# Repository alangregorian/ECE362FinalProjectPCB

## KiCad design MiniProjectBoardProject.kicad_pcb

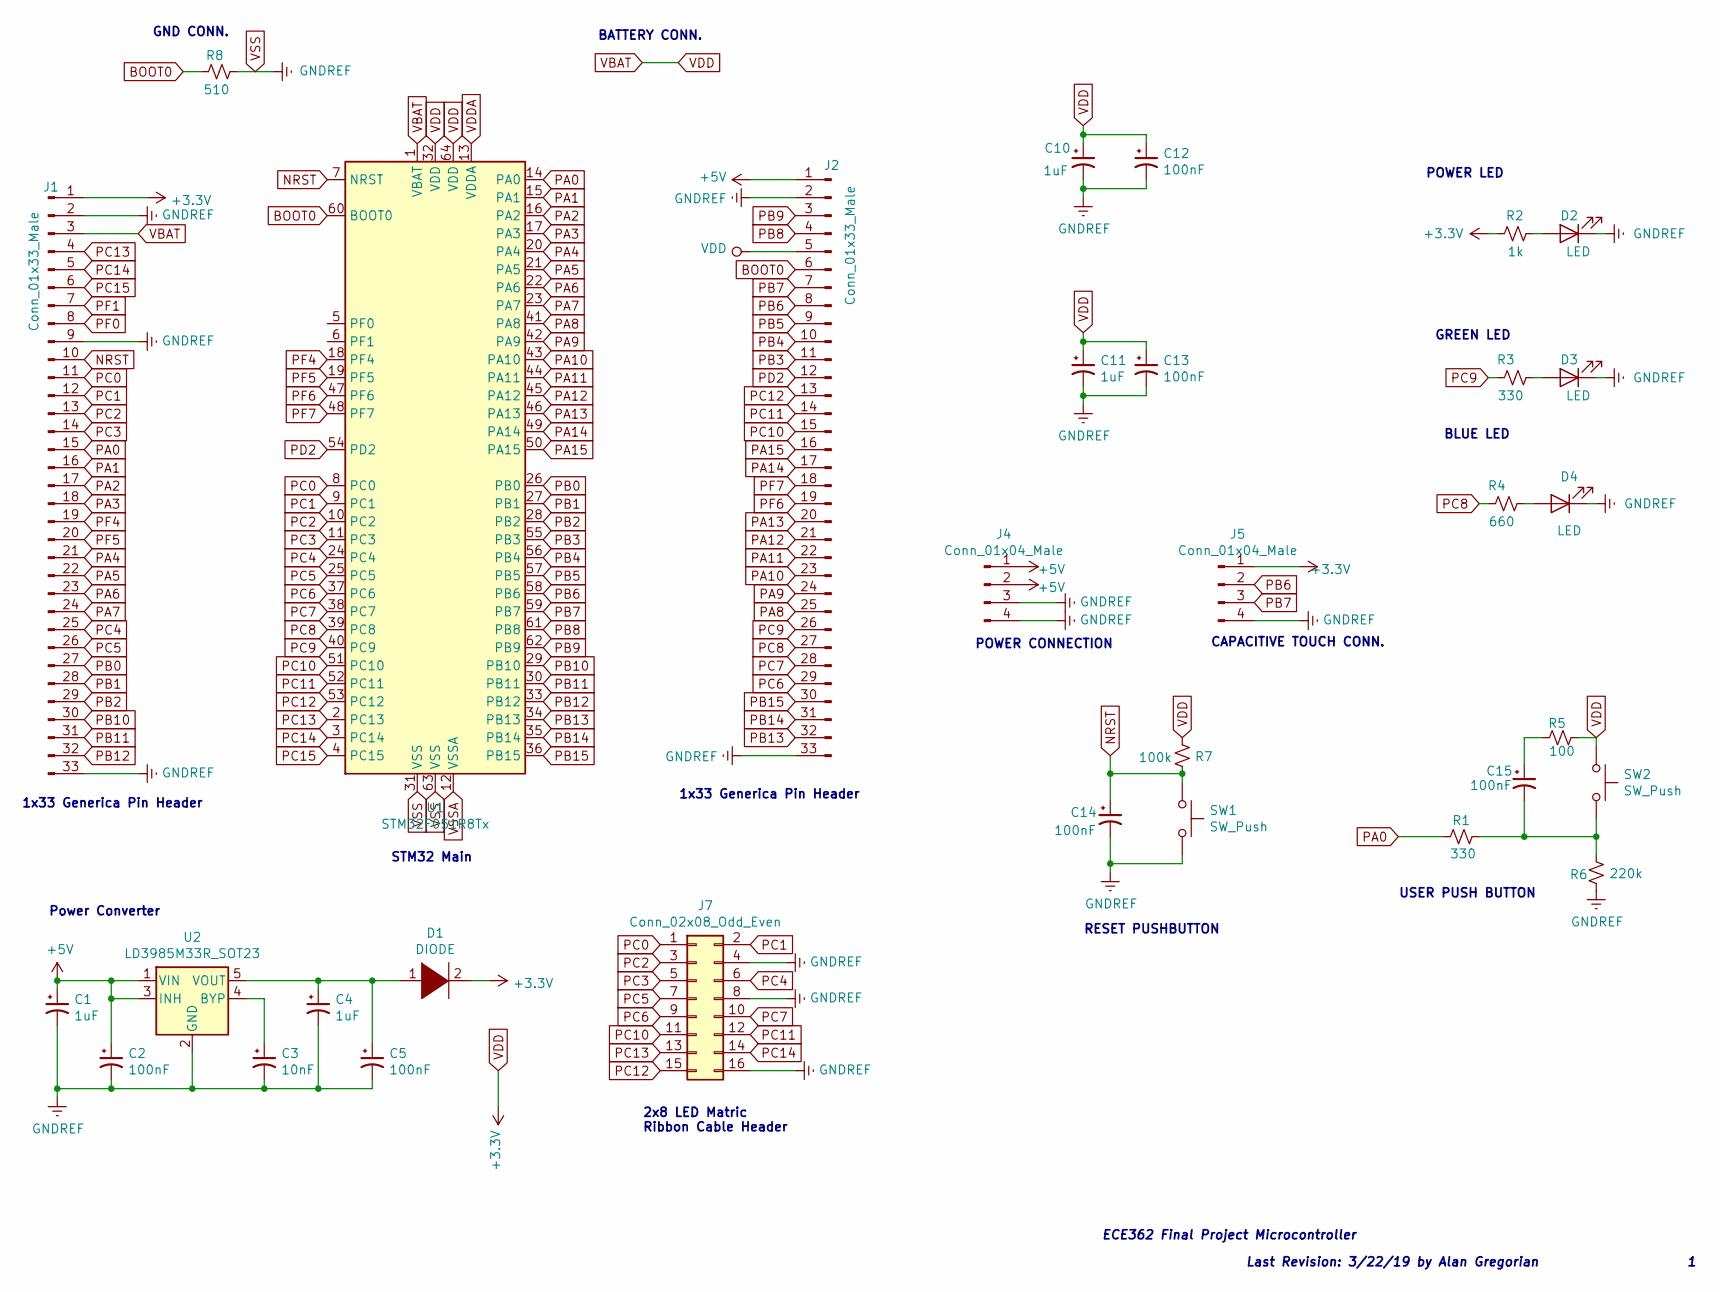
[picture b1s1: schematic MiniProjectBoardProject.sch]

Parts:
C1, C4, C10, C11: 1uF; C_0201_0603Metric
C2, C5, C12, C13, C14, C15: 100nF; C_0201_0603Metric
C3: 10nF; C_0201_0603Metric
D1: DIODE; D_SOD-323
D2, D3, D4: LED; LED_1206_3216Metric
J1, J2: Conn_01x33_Male; PinSocket_1x33_P2.54mm_Vertical
J4, J5: Conn_01x04_Male; PinSocket_1x04_P2.54mm_Vertical
J7: Conn_02x08_Odd_Even; PinSocket_2x08_P2.54mm_Vertical
R1, R3: 330; R_0603_1608Metric
R2: 1k; R_0603_1608Metric
R4: 660; R_0603_1608Metric
R5: 100; R_0603_1608Metric
R6: 220k; R_0603_1608Metric
R7: 100k; R_0603_1608Metric
R8: 510; R_0603_1608Metric
SW1, SW2: SW_Push; SW_PUSH_6mm
U1: STM32F051R8Tx; LQFP-64_10x10mm_P0.5mm
U2: LD3985M33R_SOT23; SOT-23-5

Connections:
+5V: C1.1, C2.1, J2.1, J4.1, J4.2, U2.1 (VIN), U2.3 (INH)
BOOT0: J2.6, R8.1, U1.60 (BOOT0)
NRST: C14.1, J1.10, R7.1, SW1.1, U1.7 (NRST)
unnamed: C3.1, U2.4 (BYP)
unnamed: C4.1, C5.1, D1.1 (K), U2.5 (VOUT)
unnamed: C15.1, R5.2
unnamed: C15.2, R1.1, R6.2, SW2.2
unnamed: D2.2 (A), R2.1
unnamed: D3.2 (A), R3.1
unnamed: D4.2 (A), R4.1
PA0: J1.15, R1.2, U1.14 (PA0)
PA1: J1.16, U1.15 (PA1)
PA2: J1.17, U1.16 (PA2)
PA3: J1.18, U1.17 (PA3)
PA4: J1.21, U1.20 (PA4)
PA5: J1.22, U1.21 (PA5)
PA6: J1.23, U1.22 (PA6)
PA7: J1.24, U1.23 (PA7)
PA8: J2.25, U1.41 (PA8)
PA9: J2.24, U1.42 (PA9)
PA10: J2.23, U1.43 (PA10)
PA11: J2.22, U1.44 (PA11)
PA12: J2.21, U1.45 (PA12)
PA13: J2.20, U1.46 (PA13)
PA14: J2.17, U1.49 (PA14)
PA15: J2.16, U1.50 (PA15)
PB0: J1.27, U1.26 (PB0)
PB1: J1.28, U1.27 (PB1)
PB2: J1.29, U1.28 (PB2)
PB3: J2.11, U1.55 (PB3)
PB4: J2.10, U1.56 (PB4)
PB5: J2.9, U1.57 (PB5)
PB6: J2.8, J5.2, U1.58 (PB6)
PB7: J2.7, J5.3, U1.59 (PB7)
PB8: J2.4, U1.61 (PB8)
PB9: J2.3, U1.62 (PB9)
PB10: J1.30, U1.29 (PB10)
PB11: J1.31, U1.30 (PB11)
PB12: J1.32, U1.33 (PB12)
PB13: J2.32, U1.34 (PB13)
PB14: J2.31, U1.35 (PB14)
PB15: J2.30, U1.36 (PB15)
PC0: J1.11, J7.1, U1.8 (PC0)
PC1: J1.12, J7.2, U1.9 (PC1)
PC2: J1.13, J7.3, U1.10 (PC2)
PC3: J1.14, J7.5, U1.11 (PC3)
PC4: J1.25, J7.6, U1.24 (PC4)
PC5: J1.26, J7.7, U1.25 (PC5)
PC6: J2.29, J7.9, U1.37 (PC6)
PC7: J2.28, J7.10, U1.38 (PC7)
PC8: J2.27, R4.2, U1.39 (PC8)
PC9: J2.26, R3.2, U1.40 (PC9)
PC10: J2.15, J7.11, U1.51 (PC10)
PC11: J2.14, J7.12, U1.52 (PC11)
PC12: J2.13, J7.15, U1.53 (PC12)
PC13: J1.4, J7.13, U1.2 (PC13)
PC14: J1.5, J7.14, U1.3 (PC14)
PC15: J1.6, U1.4 (PC15)
PD2: J2.12, U1.54 (PD2)
PF0: J1.8
PF1: J1.7
PF4: J1.19, U1.18 (PF4)
PF5: J1.20, U1.19 (PF5)
PF6: J2.19, U1.47 (PF6)
PF7: J2.18, U1.48 (PF7)
VBAT: C10.1, C11.1, C12.1, C13.1, D1.2 (A), J1.1, J1.3, J2.5, J5.1, R2.2, R5.1, R7.2, SW2.1, U1.1 (VBAT), U1.32 (VDD), U1.64 (VDD)
VDDA: U1.13 (VDDA)
VSS: C1.2, C2.2, C3.2, C4.2, C5.2, C10.2, C11.2, C12.2, C13.2, C14.2, D2.1 (K), D3.1 (K), D4.1 (K), J1.2, J1.9, J1.33, J2.2, J2.33, J4.3, J4.4, J5.4, J7.4, J7.8, J7.16, R6.1, R8.2, SW1.2, U1.31 (VSS), U1.63 (VSS), U2.2 (GND); also elsewhere on the board
VSSA: U1.12 (VSSA)

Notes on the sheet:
USER PUSH BUTTON
GREEN LED
BLUE LED
POWER LED
Power Converter
ECE362 Final Project Microcontroller
Last Revision: 3/22/19 by Alan Gregorian
1x33 Generica Pin Header
STM32 Main
POWER CONNECTION
CAPACITIVE TOUCH CONN.
BATTERY CONN.
GND CONN.
2x8 LED Matric Ribbon Cable Header
RESET PUSHBUTTON

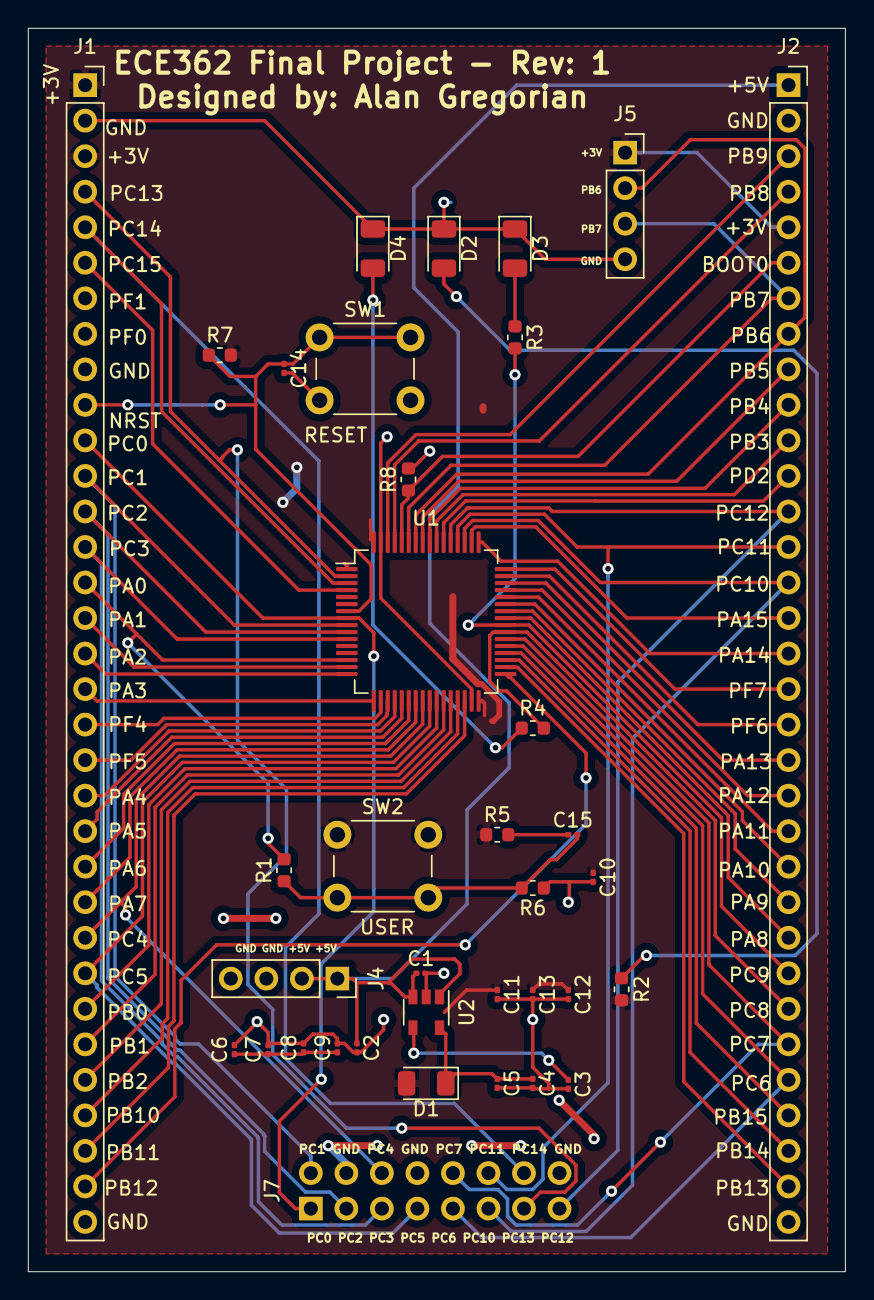
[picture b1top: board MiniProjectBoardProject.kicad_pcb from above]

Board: 2 copper layers, 58.4 x 88.9 mm, 36 parts (1 on the bottom side), 66 nets.

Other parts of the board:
C6, C7, C8, C9: 100nF; C_0201_0603Metric

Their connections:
+3V3: C6.1, C7.1, C8.1, C9.1
VSS: C6.2, C7.2, C8.2, C9.2; also elsewhere on the board

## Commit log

2019-03-31 Finished PCB, missing Gerber
2019-03-31 Gerber Generated
